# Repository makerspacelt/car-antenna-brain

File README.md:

car-antenna-brain
=================

Car antenna motor controller

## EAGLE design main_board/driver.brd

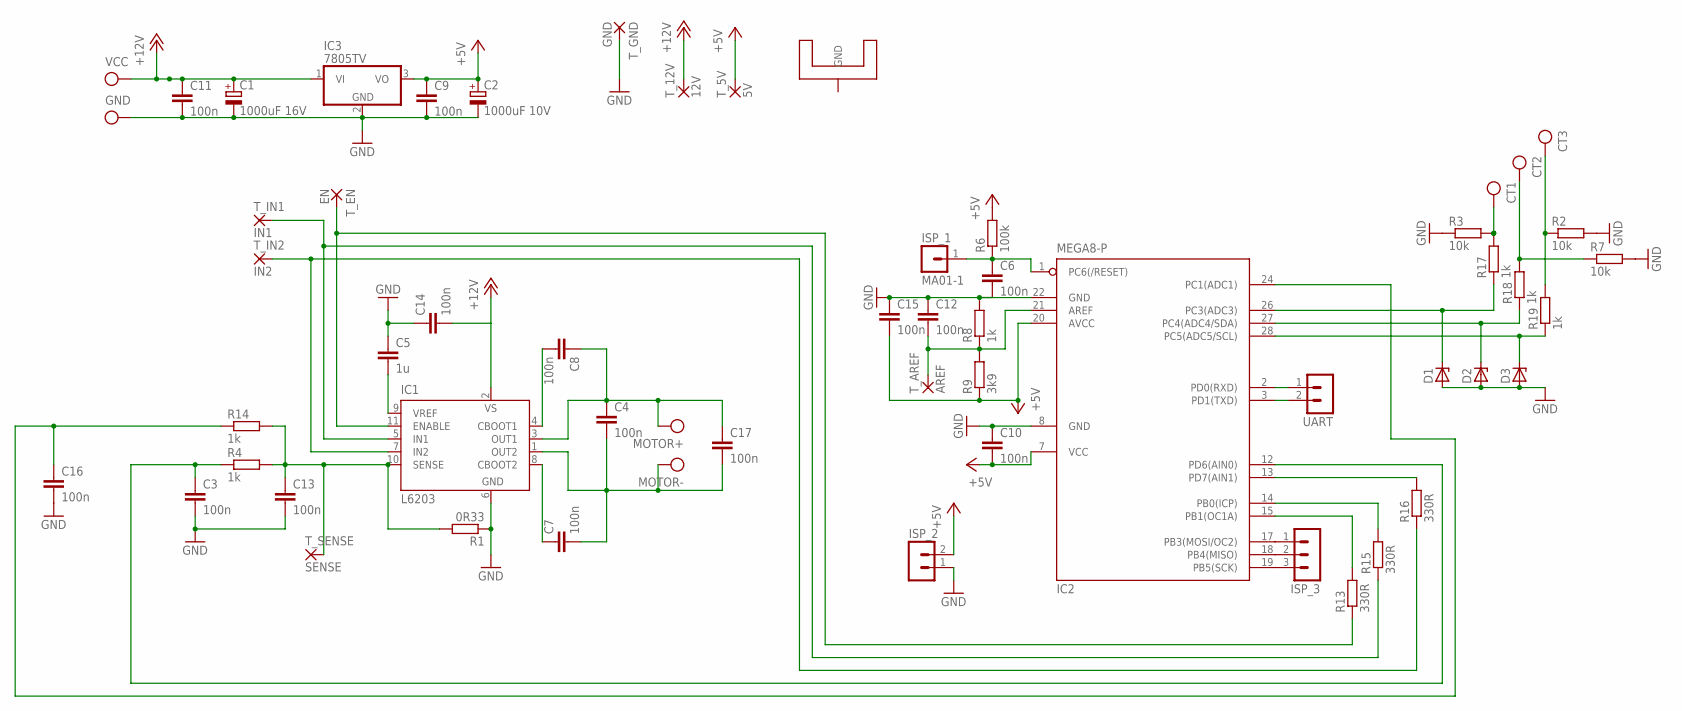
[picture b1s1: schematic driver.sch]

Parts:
C1: 1000uF 16V; E5-10,5
C2: 1000uF 10V; E5-10,5
C3, C6, C8, C9, C10, C11, C12, C13, C14, C15, C16, C17: 100n; C0805K
C4: 100n; C050-024X044
C5: 1u; C0805K
C7: 100n; C075-032X103
CT1, CT2, CT3: PIN_X
D1, D2, D3: ZENER-DIODESOD80C; SOD80C
GND: PIN_X
IC1: L6203; MULTIWATT-11
IC2: MEGA8-P; DIL28-3
IC3: 7805TV; TO220V
ISP_1: MA01-1
ISP_2: MA02-1
ISP_3: MA03-1
MOTOR+: PIN_X
MOTOR-: PIN_X
R1: 0R33; 0922/22
R2, R3, R7: 10k; R0805W
R4, R8, R14, R17, R18, R19: 1k; R0805W
R6: 100k; R0805W
R9: 3k9; R0805W
R13: 330R; 0207/12
R15, R16: 330R; R0805W
T_5V: 5V; 2,15/1,0
T_12V: 12V; 2,15/1,0
T_AREF: AREF; 2,15/1,0
T_EN: EN; 2,15/1,0
T_GND: GND; 2,15/1,0
T_IN1: IN1; 2,15/1,0
T_IN2: IN2; 2,15/1,0
T_SENSE: SENSE; 2,15/1,0
U$1: HEATSINK_CAR_ANTENNA
UART: MA02-1
VCC: VCC; PIN_X

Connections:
+5V: C2.+, C9.1, C10.2, C15.2, IC2.7 (VCC), IC2.20 (AVCC), IC3.3 (VO), ISP_2.2 (3), R6.2, R9.1, T_5V.1
+12V: C1.+, C11.1, C14.2, IC1.2 (VS), IC3.1 (VI), T_12V.1, VCC.P$7
GND: C1.-, C2.-, C3.2, C5.1, C6.2, C9.2, C10.1, C11.2, C12.1, C13.2, C14.1, C15.1, C16.2, D1.A, D2.A, D3.A, GND.P$7, IC1.6 (GND), IC2.8 (GND), IC2.22 (GND), IC3.2 (GND), ISP_2.1 (2), R1.1, R2.2, R3.1, R7.2, R8.2, T_GND.1, U$1.CENTER, U$1.LEFT, U$1.RIGHT
unnamed: CT3.P$7, R2.1, R19.2
unnamed: CT1.P$7, R3.2, R17.2
unnamed: C4.1, C8.1, C17.1, IC1.3 (OUT1), MOTOR+.P$7
unnamed: C7.1, IC1.8 (CBOOT2)
unnamed: CT2.P$7, R7.1, R18.2
unnamed: D1.C, IC2.26 (PC3(ADC3)), R17.1
unnamed: C13.1, IC1.10 (SENSE), R1.2, R4.2, R14.2, T_SENSE.1
unnamed: C8.2, IC1.4 (CBOOT1)
unnamed: C5.2, IC1.9 (VREF)
unnamed: C4.2, C7.2, C17.2, IC1.1 (OUT2), MOTOR-.P$7
unnamed: C3.1, IC2.12 (PD6(AIN0)), R4.1
unnamed: IC1.7 (IN2), R16.1, T_IN2.1
unnamed: IC1.11 (ENABLE), R13.1, T_EN.1
unnamed: IC1.5 (IN1), R15.1, T_IN1.1
unnamed: IC2.15 (PB1(OC1A)), R13.2
unnamed: IC2.17 (PB3(MOSI/OC2)), ISP_3.1
unnamed: IC2.18 (PB4(MISO)), ISP_3.2
unnamed: C12.2, IC2.21 (AREF), R8.1, R9.2, T_AREF.1
unnamed: IC2.19 (PB5(SCK)), ISP_3.3
unnamed: IC2.2 (PD0(RXD)), UART.1 (2)
unnamed: IC2.3 (PD1(TXD)), UART.2 (3)
unnamed: C16.1, IC2.24 (PC1(ADC1)), R14.1
unnamed: IC2.14 (PB0(ICP)), R15.2
unnamed: IC2.13 (PD7(AIN1)), R16.2
unnamed: C6.1, IC2.1 (PC6(/RESET)), ISP_1.1, R6.1
unnamed: D2.C, IC2.27 (PC4(ADC4/SDA)), R18.1
unnamed: D3.C, IC2.28 (PC5(ADC5/SCL)), R19.1

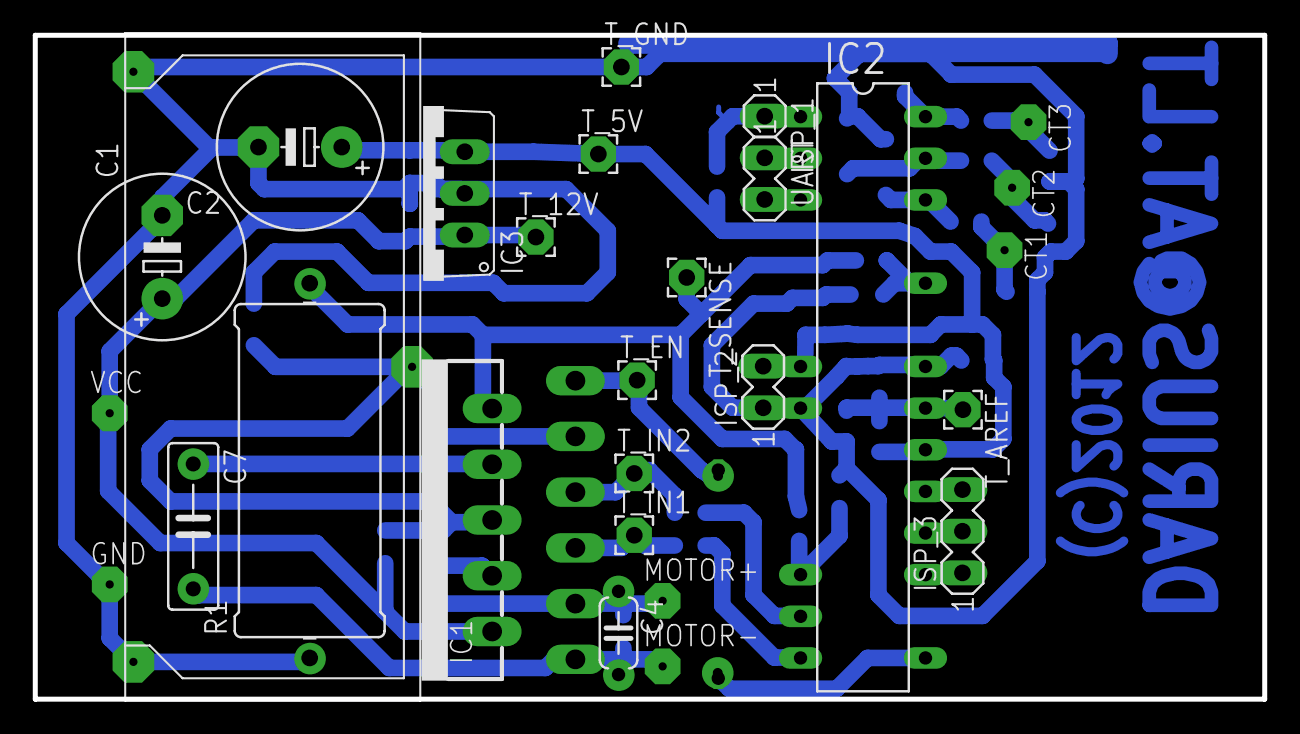
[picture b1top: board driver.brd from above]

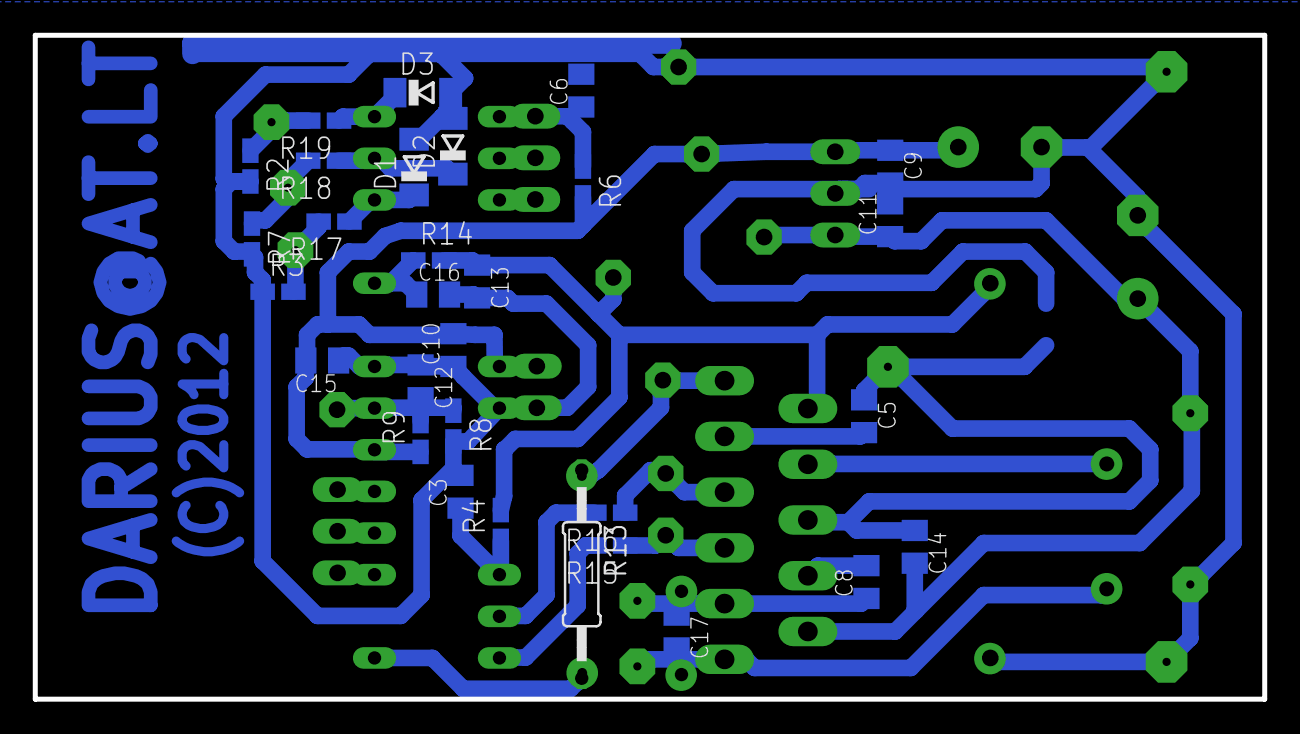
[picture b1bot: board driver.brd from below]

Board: 2 copper layers, 75.0 x 40.5 mm, 58 parts (30 on the bottom side), 30 nets.

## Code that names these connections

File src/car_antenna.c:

#define F_CPU 8000000UL
#define MAX_I 800U

#define AUTO_UP     0b110
#define AUTO_DOWN   0b000
#define MANUAL_UP   0b111
#define MANUAL_DOWN 0b010

#define PWM OCR1A
#define ADC ADCW

#include "avr/io.h"
#include "avr/interrupt.h"
#include "stdlib.h"
#include <util/delay.h>
#include "comport.c"


uint8_t time = 100;

volatile uint16_t startup_current_counter = 0;
volatile uint8_t can_move_motor = 0;

volatile uint8_t button_debounce_counter[8] = { 0 };
volatile uint8_t button_state_cutrrent = 0;
volatile uint8_t button_state_last = 0;
volatile uint8_t is_in_transition = 0;



void pullAntennaDown(void) {
	comport_writeln("Pulling antenna down <<<     ");
	PORTD |= 1<<7;
	PORTB &= ~(1<<0);
	PWM = 0xFF;
	can_move_motor = 1;
}

void pushAntennaUp(void) {
	comport_writeln("Pushing antenna up >>>     ");
	PORTD &= ~(1<<7);
	PORTB |= 1<<0;
	PWM = 0xFF;
	can_move_motor = 1;
}

void stopMotor(void) {
	comport_writeln("Stopping the motor ---     ");
	can_move_motor = 0;
}

void printStatus(void) {
	time++;
	if (time>198) time=100;

	comport_writenum(time,10);
	comport_write(" PWM:");
	comport_writenum(PWM,10);
	comport_write(" ADC:");
	comport_writenum(ADC,10);
	comport_write("     ");
	comport_writenum( (PINC & (0b111<<3))>>3 ,2);
	comport_write("    modes: ");
	comport_writenum(button_debounce_counter[AUTO_UP],10);
	comport_write(" ");
	comport_writenum(button_debounce_counter[MANUAL_UP],10);
	comport_write(" -  ");
	comport_writenum(button_debounce_counter[MANUAL_DOWN],10);
	comport_write(" ");
	comport_writenum(button_debounce_counter[AUTO_DOWN],10);
	comport_write("    button states, last: ");
	comport_writenum(button_state_last,10);
	comport_write(" , current: ");
	comport_writenum(button_state_cutrrent,10);

	comport_write("     ");
	comport_send(13);
}

ISR(ADC_vect) {

	// check for counterforce
	if (ADC > MAX_I-100) {
		startup_current_counter++;
	} else {
		startup_current_counter = 0;
	}
	if (startup_current_counter > 0x00ff) {
		stopMotor();
		startup_current_counter = 0;
	}
	// adjust PWM to match desired current
	if (can_move_motor) {
		if (ADC < MAX_I) {
			if (PWM < 255) {
				PWM++;
			}
		} else {
			if (PWM > 0) {
				PWM--;
			}
		}
	} else {
		PWM = 0;
	}
	// read buttons (PC3 PC4 PC5)
	uint8_t tmp = (PINC & (0b111<<3))>>3;
	uint8_t i = 0;
	for (i=0; i<8; i++) {
		if (tmp==i) {
			if (button_debounce_counter[i] < 255) {
				button_debounce_counter[i]++;
			} else {
				// got seteled combination
				if (button_state_cutrrent != i) {
					button_state_last = button_state_cutrrent;
					button_state_cutrrent = i;
					is_in_transition = 1;
				}
			}
		} else {
			button_debounce_counter[i] = 0;
		}
	}
}

void setup() {
	// init comport communications with no interrupts
	comport_init(BAUD_9600,0,0);

	// init PWM stuff in Timer1
	DDRB |= 1<<1;             // setting PWM pin as output
	PWM = 0x00;               // setting PWM to 0
	TCCR1A = 0b10100001;      // page 97 
	TCCR1B = 0b00001001;      // page 98

	// init ADC conversion
	ADMUX = 0b00000001;       // external Vref; ADC1 input
	ADCSRA = (1<<ADEN) | (1<<ADPS2) | (1<<ADPS1) | (1<<ADPS0); // Enable and set prescaler to 128 
	ADCSRA |= (1<<ADFR);      // Free-running mode
	ADCSRA |= (1<<ADSC);      // Start converting
	ADCSRA |= (1<<ADIE);      // Interrupt enabled

	// motor direction outputs (PB0 and PD7)
	DDRB |= 1<<0;             // Antenna direction DOWN
	DDRD |= 1<<7;             // Antenna direction UP

	// control inputs (PC3 PC4 PC5)
	DDRC &= ~(1<<3);
	DDRC &= ~(1<<4);
	DDRC &= ~(1<<5);

	comport_writeln("Automatic Car Antenna by <darius@at.lt>");
	comport_writeln("BOOTED UP!");

	// enable global interrupts
	sei();
}

int main(void) {

	setup();

	while (1) {
		if (is_in_transition) {
			comport_writeln("\ngot transition");
			is_in_transition = 0;

			if ((button_state_last==MANUAL_DOWN && button_state_cutrrent==AUTO_UP)
			||  (button_state_last==MANUAL_DOWN && button_state_cutrrent==AUTO_DOWN)
			||  (button_state_last==MANUAL_UP   && button_state_cutrrent==AUTO_UP)
			||  (button_state_last==MANUAL_UP   && button_state_cutrrent==AUTO_DOWN)
			) {
					stopMotor();
			} else
			if ((button_state_last==AUTO_UP   && button_state_cutrrent==AUTO_DOWN)
			||  (button_state_last==AUTO_UP   && button_state_cutrrent==MANUAL_DOWN)
			||  (button_state_last==AUTO_DOWN && button_state_cutrrent==MANUAL_DOWN)
			||  (button_state_last==MANUAL_UP && button_state_cutrrent==MANUAL_DOWN)
			) {
					pullAntennaDown();
			} else 
			if ((button_state_last==AUTO_UP     && button_state_cutrrent==MANUAL_UP)
			||  (button_state_last==AUTO_DOWN   && button_state_cutrrent==AUTO_UP)
			||  (button_state_last==AUTO_DOWN   && button_state_cutrrent==MANUAL_UP)
			||  (button_state_last==MANUAL_DOWN && button_state_cutrrent==MANUAL_UP)
			) {
					pushAntennaUp();
			}
		} else {
			printStatus();
		}
	}
	return 1;
}

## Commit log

2014-04-19 adding first version of the project
2014-04-20 ignoring files that can be compiled from source
2014-04-20 adding old source with makefile
2014-04-20 adding compiled ready-to-upload hex file
2014-04-21 refactoring at will to make code more maintainable
2014-07-05 adding netbeans project to gitignore

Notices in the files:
main_board/driver.brd:
(C)2012
